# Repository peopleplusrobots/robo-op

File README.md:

## Robo.Op
### Industrial Robots. Open for Creativity.

_Robo.Op_ is an open hardware / open software platform for hacking industrial robots (IRs). 
_Robo.Op_ makes it cheaper and easier to customize your IR for creative use, so you can _explore the fringes of industrial robotics_.
<br/><br/>
_See [this](https://github.com/peopleplusrobots/robo-op/wiki/3.-Software:-Getting-Started-Tutorial) tutorial to get started._
<br/><br/>

<br/><br/>
We built _Robo.Op_ to bypass the expensive, proprietary software and hardware currently offered by robotics companies. _Robo.Op_ enables artists and designers to _(a)_ develop affordable custom tools for creative robotics, and _(b)_ share tools and knowledge across robotic platforms.
<br/><br/>
_Robo.Op_ is made of three components:<br/>
<ul>
<li>The Robot Tool Adaptor (RTA) – a universal adaptor sheild for developing affordable, custom tools for creative robotics.</li>
<li>A Processing Interface – a simplified, modular software interface for cross-platform programming of IRs.</li>
<li>A Centralized Knowledge Hub - this github-hosted project for sharing knowledge, tools, and code.</li>
</ul>

> The full Project Overview can be found [here](https://github.com/peopleplusrobots/robo-op/wiki/1.-Project-Overview).

#### Opening Hardware
For tutorials on adapting, fabricating, & assembling your RTA, click [here](https://github.com/peopleplusrobots/robo-op/wiki/2.-Hardware:-Design,-Fabrication-&-Assembly).

To download the RTA fabrication files, click [here](https://github.com/peopleplusrobots/robo-op/tree/master/robo-op/for%20ABB%20robots/fabrication%20files).

#### Opening Software
For tutorials for using our Processing Interface to control your IR, click [here](https://github.com/peopleplusrobots/robo-op/wiki/3.-Software:-Workflow-&-Integration).

To download the code, click [here](https://github.com/peopleplusrobots/robo-op/tree/master/robo-op/for%20ABB%20robots/code).

#### Sharing Knowledge
Visit the [wiki](https://github.com/peopleplusrobots/robo-op/wiki) for resources related to *Robo.Op* and creative robotics.

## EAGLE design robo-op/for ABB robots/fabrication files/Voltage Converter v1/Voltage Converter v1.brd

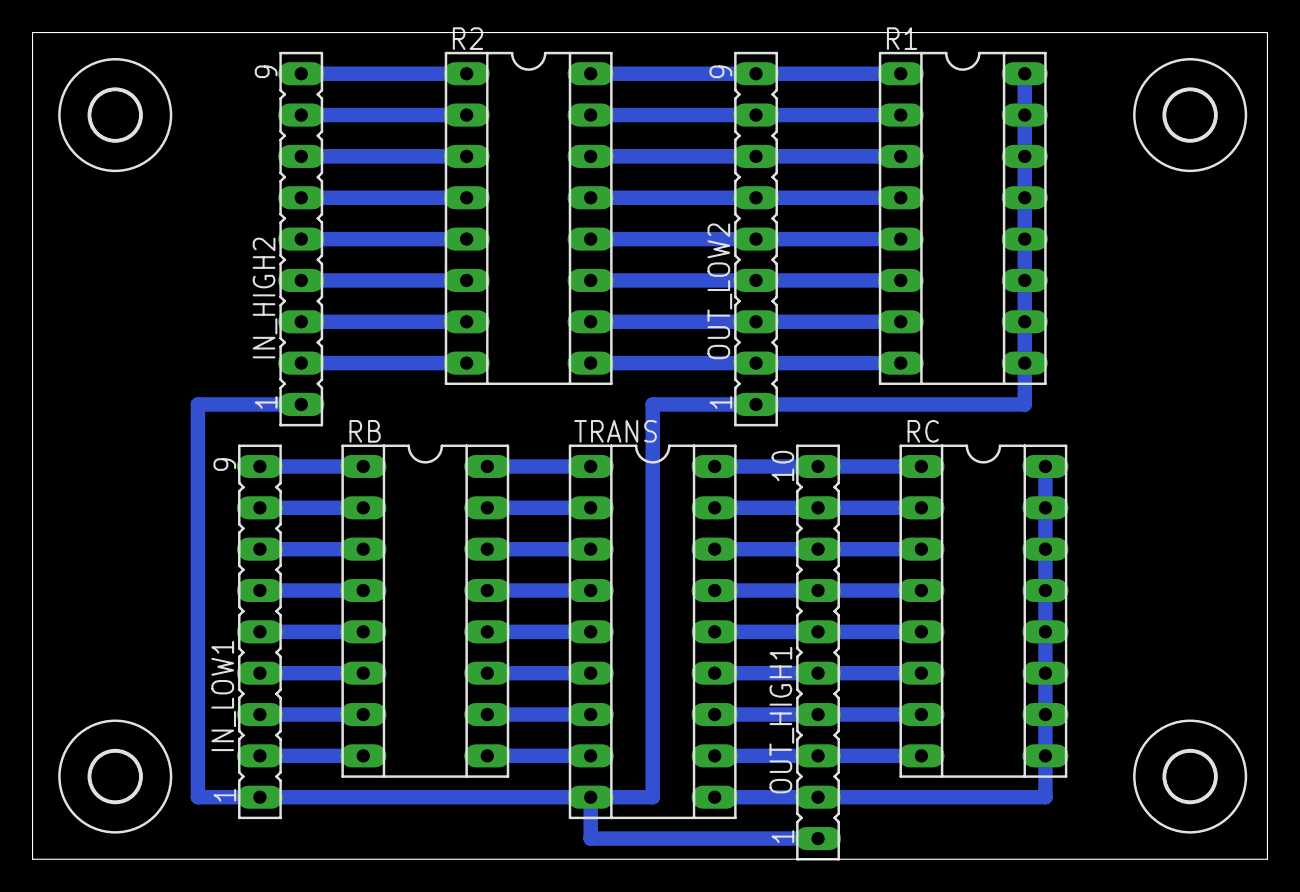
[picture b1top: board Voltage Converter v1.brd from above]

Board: 2 copper layers, 75.9 x 50.8 mm, 13 parts (0 on the bottom side), 42 nets.

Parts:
IN_HIGH2: FE09
IN_LOW1: FE09
OUT_HIGH1: FE10
OUT_LOW2: FE09
R1, R2: SOCKET-16
RB: SOCKET-16
RC: SOCKET-16
TRANS: SOCKET-18
U$1, U$2, U$3, U$4: 3,0

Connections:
GND: IN_HIGH2.1, IN_LOW1.1, OUT_HIGH1.1, OUT_LOW2.1, R1.9, R1.10, R1.11, R1.12, R1.13, R1.14, R1.15, R1.16, TRANS.9
unnamed: IN_LOW1.2, RB.8
unnamed: IN_LOW1.3, RB.7
unnamed: IN_LOW1.4, RB.6
unnamed: IN_LOW1.5, RB.5
unnamed: IN_LOW1.6, RB.4
unnamed: IN_LOW1.7, RB.3
unnamed: IN_LOW1.8, RB.2
unnamed: IN_LOW1.9, RB.1
unnamed: RB.9, TRANS.8
unnamed: RB.10, TRANS.7
unnamed: RB.11, TRANS.6
unnamed: RB.12, TRANS.5
unnamed: RB.13, TRANS.4
unnamed: RB.14, TRANS.3
unnamed: RB.15, TRANS.2
unnamed: RB.16, TRANS.1
unnamed: OUT_HIGH1.10, RC.1, TRANS.18
unnamed: OUT_HIGH1.9, RC.2, TRANS.17
unnamed: OUT_HIGH1.8, RC.3, TRANS.16
unnamed: OUT_HIGH1.7, RC.4, TRANS.15
unnamed: OUT_HIGH1.6, RC.5, TRANS.14
unnamed: OUT_HIGH1.5, RC.6, TRANS.13
unnamed: OUT_HIGH1.4, RC.7, TRANS.12
unnamed: OUT_HIGH1.3, RC.8, TRANS.11
unnamed: IN_HIGH2.2, R2.8
unnamed: IN_HIGH2.3, R2.7
unnamed: IN_HIGH2.4, R2.6
unnamed: IN_HIGH2.5, R2.5
unnamed: IN_HIGH2.6, R2.4
unnamed: IN_HIGH2.7, R2.3
unnamed: IN_HIGH2.8, R2.2
unnamed: IN_HIGH2.9, R2.1
unnamed: OUT_LOW2.9, R1.1, R2.16
unnamed: OUT_LOW2.8, R1.2, R2.15
unnamed: OUT_LOW2.7, R1.3, R2.14
unnamed: OUT_LOW2.6, R1.4, R2.13
unnamed: OUT_LOW2.5, R1.5, R2.12
unnamed: OUT_LOW2.4, R1.6, R2.11
unnamed: OUT_LOW2.3, R1.7, R2.10
unnamed: OUT_LOW2.2, R1.8, R2.9
VCC: OUT_HIGH1.2, RC.9, RC.10, RC.11, RC.12, RC.13, RC.14, RC.15, RC.16, TRANS.10

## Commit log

2014-09-06 intial commit
2014-09-06 restructured communication in server and eclipse project
2014-09-09 Create gh-pages branch via GitHub
2014-09-13 built out Robot.java and Server.mod
2014-09-14 added OSC communication
2014-09-25 changed Arduino class to Serial class
2014-09-25 updated project name
2014-09-25 updated read me
2014-09-25 updated wiki
2014-09-25 moved into robo-op folder
2014-09-29 added fabrication files
2014-09-29 added software diagram
2014-09-29 updated software diagram
2014-09-29 added assembly and cut files
2014-10-07 organized repo and cleaned up template code
2014-10-18 updated REAME
2015-05-07 Added GettingStarted project to repo
2015-05-07 added font back to data folder
2015-05-07 Added example projects
    These are not well documented, yet.
2015-05-18 broken link fixed
2016-02-24 updated gh
